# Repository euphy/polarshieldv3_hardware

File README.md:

View this project on [CADLAB.io](https://cadlab.io/project/1157). 

# polarshieldv3_hardware
Schematics, board and gerbers for Polarshield v3

Polarshield v3 is an aggregation board for connecting

* NodeMCU-32S
* 2x stepper drivers
* 320x240 LCD
* Touch panel
* SD card

v3.0e is the currently manufactured version that's inside recent PolargraphSD machines.

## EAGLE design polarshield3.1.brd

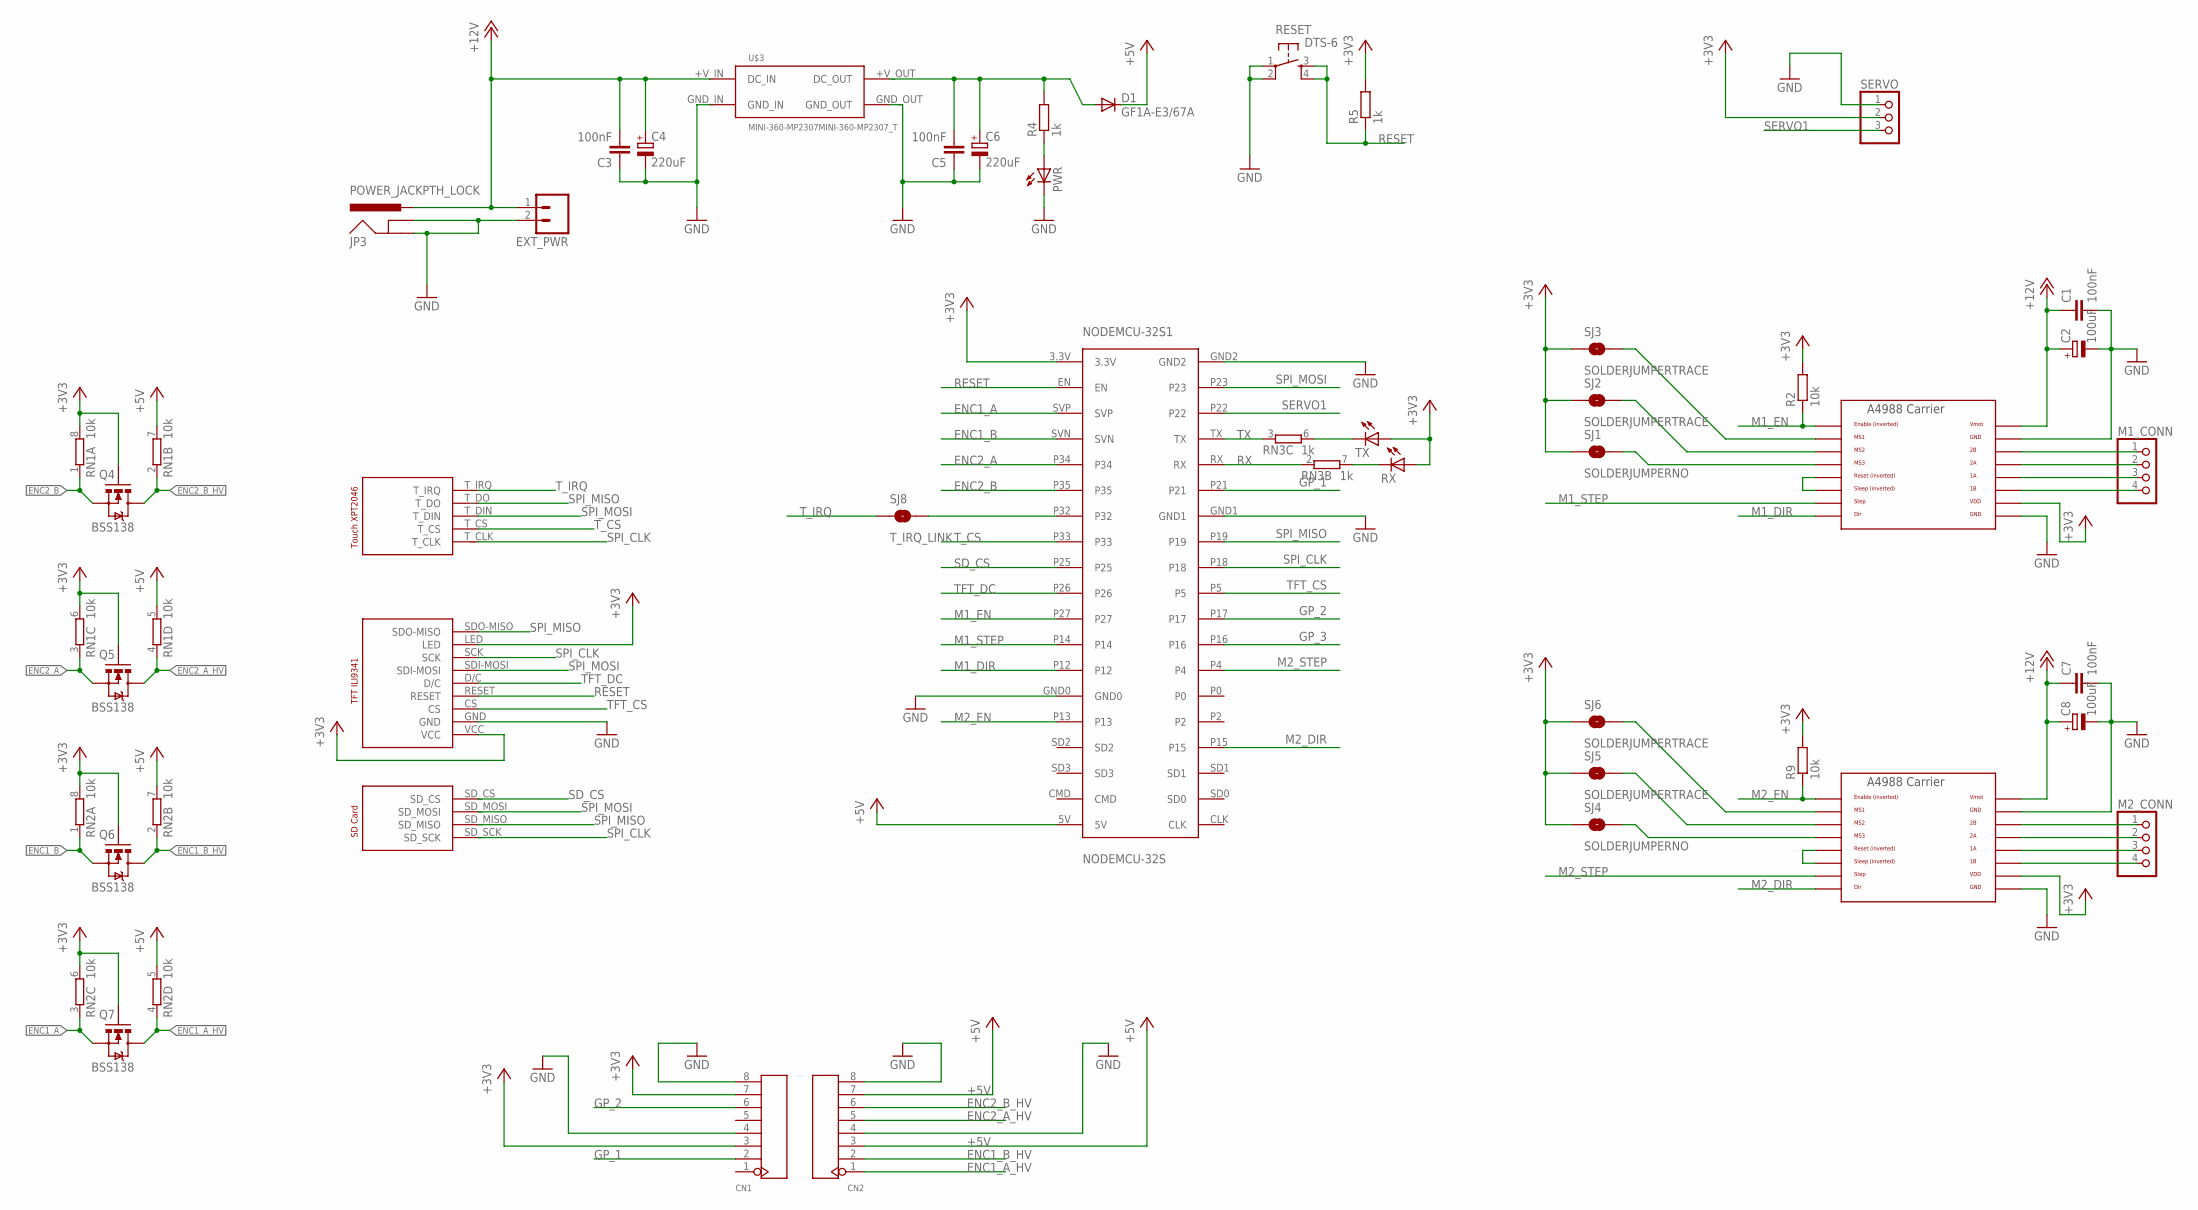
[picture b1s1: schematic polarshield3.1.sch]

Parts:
C1, C3, C5, C7: 100nF; C0805
C2, C8: 100uF; 153CLV-0605
C4, C6: 220uF; 153CLV-0605
CN1, CN2: DIP-BLACK-FEMALE-HEADER-VERT(8P-2.54); H8-2.54
D1: GF1A-E3/67A; DO214BA
EXT_PWR: M02PTH; 1X02
JP3: POWER_JACKPTH_LOCK; POWER_JACK_PTH_LOCK
M1_CONN, M2_CONN: PINHD-1X4/90; 1X04/90
MOTOR_1, MOTOR_2: A4988BREAKOUT
NODEMCU-32S1: NODEMCU-32S
PWR: LEDCHIPLED_0805; CHIPLED_0805
Q4, Q5, Q6, Q7: BSS138; SOT23-3
R2, R9: 10k; M0805
R4, R5: 1k; M0805
RESET: DTS-6
RN1, RN2: 10k; EXB38V
RN3: 1k; EXB38V
RX: LEDCHIPLED_0805; CHIPLED_0805
SERVO: PINHD-1X3/90; 1X03/90
SJ1, SJ4: SOLDERJUMPERNO; SJ_2S-NO
SJ2, SJ3, SJ5, SJ6: SOLDERJUMPERTRACE; SJ_2S-TRACE
SJ8: T_IRQ_LINK; SJ_2S-NO
TX: LEDCHIPLED_0805; CHIPLED_0805
U$2: 2.4_TFT_SPI_TOUCH_SD
U$3: MINI-360-MP2307MINI-360-MP2307_T; MINI-360-MP2307

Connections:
+3V3: CN1.3, CN1.7, MOTOR_1.VDD, MOTOR_2.VDD, NODEMCU-32S1.3.3V, Q4.1 (G), Q5.1 (G), Q6.1 (G), Q7.1 (G), R2.2, R5.2, R9.2, RN1.6 (2), RN1.8 (2), RN2.6 (2), RN2.8 (2), RX.A, SERVO.2, SJ1.1, SJ2.1, SJ3.1, SJ4.1, SJ5.1, SJ6.1, TX.A, U$2.LED, U$2.VCC
+5V: CN2.3, CN2.7, D1.C, NODEMCU-32S1.5V, RN1.5 (2), RN1.7 (2), RN2.5 (2), RN2.7 (2)
+12V: C1.1, C2.+, C3.2, C4.+, C7.1, C8.+, EXT_PWR.1, JP3.PWR, MOTOR_1.VMOT, MOTOR_2.VMOT, U$3.+V_IN (DC_IN)
ENC1_A: NODEMCU-32S1.SVP, Q7.2 (S), RN2.3 (1)
ENC1_A_HV: CN2.1, Q7.3 (D), RN2.4 (1)
ENC1_B: NODEMCU-32S1.SVN, Q6.2 (S), RN2.1
ENC1_B_HV: CN2.2, Q6.3 (D), RN2.2 (1)
ENC2_A: NODEMCU-32S1.P34, Q5.2 (S), RN1.3 (1)
ENC2_A_HV: CN2.5, Q5.3 (D), RN1.4 (1)
ENC2_B: NODEMCU-32S1.P35, Q4.2 (S), RN1.1
ENC2_B_HV: CN2.6, Q4.3 (D), RN1.2 (1)
GND: C1.2, C2.-, C3.1, C4.-, C5.1, C6.-, C7.2, C8.-, CN1.4, CN1.8, CN2.4, CN2.8, EXT_PWR.2, JP3.GND, JP3.GNDBREAK, MOTOR_1.GND, MOTOR_1.GND@0 (GND), MOTOR_2.GND, MOTOR_2.GND@0 (GND), NODEMCU-32S1.GND0, NODEMCU-32S1.GND1, NODEMCU-32S1.GND2, PWR.C, RESET.1, RESET.2, SERVO.1, U$2.GND, U$3.GND_IN, U$3.GND_OUT
GP_1: CN1.2, NODEMCU-32S1.P21
GP_2: CN1.6, NODEMCU-32S1.P17
GP_3: NODEMCU-32S1.P16
M1_DIR: MOTOR_1.DIR, NODEMCU-32S1.P12
M1_EN: MOTOR_1.EN, NODEMCU-32S1.P27, R2.1
M1_STEP: MOTOR_1.STEP, NODEMCU-32S1.P14
M2_DIR: MOTOR_2.DIR, NODEMCU-32S1.P15
M2_EN: MOTOR_2.EN, NODEMCU-32S1.P13, R9.1
M2_STEP: MOTOR_2.STEP, NODEMCU-32S1.P4
unnamed: NODEMCU-32S1.P32, SJ8.2
unnamed: MOTOR_1.RST, MOTOR_1.SLP (SLEEP)
unnamed: MOTOR_1.MS3, SJ1.2
unnamed: MOTOR_1.MS2, SJ2.2
unnamed: MOTOR_1.MS1, SJ3.2
unnamed: C5.2, C6.+, D1.A, R4.2, U$3.+V_OUT (DC_OUT)
unnamed: PWR.A, R4.1
unnamed: MOTOR_2.MS3, SJ4.2
unnamed: M1_CONN.1, MOTOR_1.2B
unnamed: M1_CONN.2, MOTOR_1.2A
unnamed: M1_CONN.3, MOTOR_1.1A
unnamed: M1_CONN.4, MOTOR_1.1B
unnamed: RN3.6 (2), TX.C
unnamed: RN3.7 (2), RX.C
unnamed: MOTOR_2.MS2, SJ5.2
unnamed: MOTOR_2.MS1, SJ6.2
unnamed: MOTOR_2.RST, MOTOR_2.SLP (SLEEP)
unnamed: M2_CONN.1, MOTOR_2.2B
unnamed: M2_CONN.2, MOTOR_2.2A
unnamed: M2_CONN.3, MOTOR_2.1A
unnamed: M2_CONN.4, MOTOR_2.1B
RESET: NODEMCU-32S1.EN, R5.1, RESET.3, RESET.4, U$2.RESET
RX: NODEMCU-32S1.RX, RN3.2 (1)
SD_CS: NODEMCU-32S1.P25, U$2.SD_CS
SERVO1: NODEMCU-32S1.P22, SERVO.3
SPI_CLK: NODEMCU-32S1.P18, U$2.SCK, U$2.SD_SCK, U$2.T_CLK
SPI_MISO: NODEMCU-32S1.P19, U$2.SDO-MISO, U$2.SD_MISO, U$2.T_DO
SPI_MOSI: NODEMCU-32S1.P23, U$2.SDI-MOSI, U$2.SD_MOSI, U$2.T_DIN
TFT_CS: NODEMCU-32S1.P5, U$2.CS
TFT_DC: NODEMCU-32S1.P26, U$2.D/C
TX: NODEMCU-32S1.TX, RN3.3 (1)
T_CS: NODEMCU-32S1.P33, U$2.T_CS
T_IRQ: SJ8.1, U$2.T_IRQ

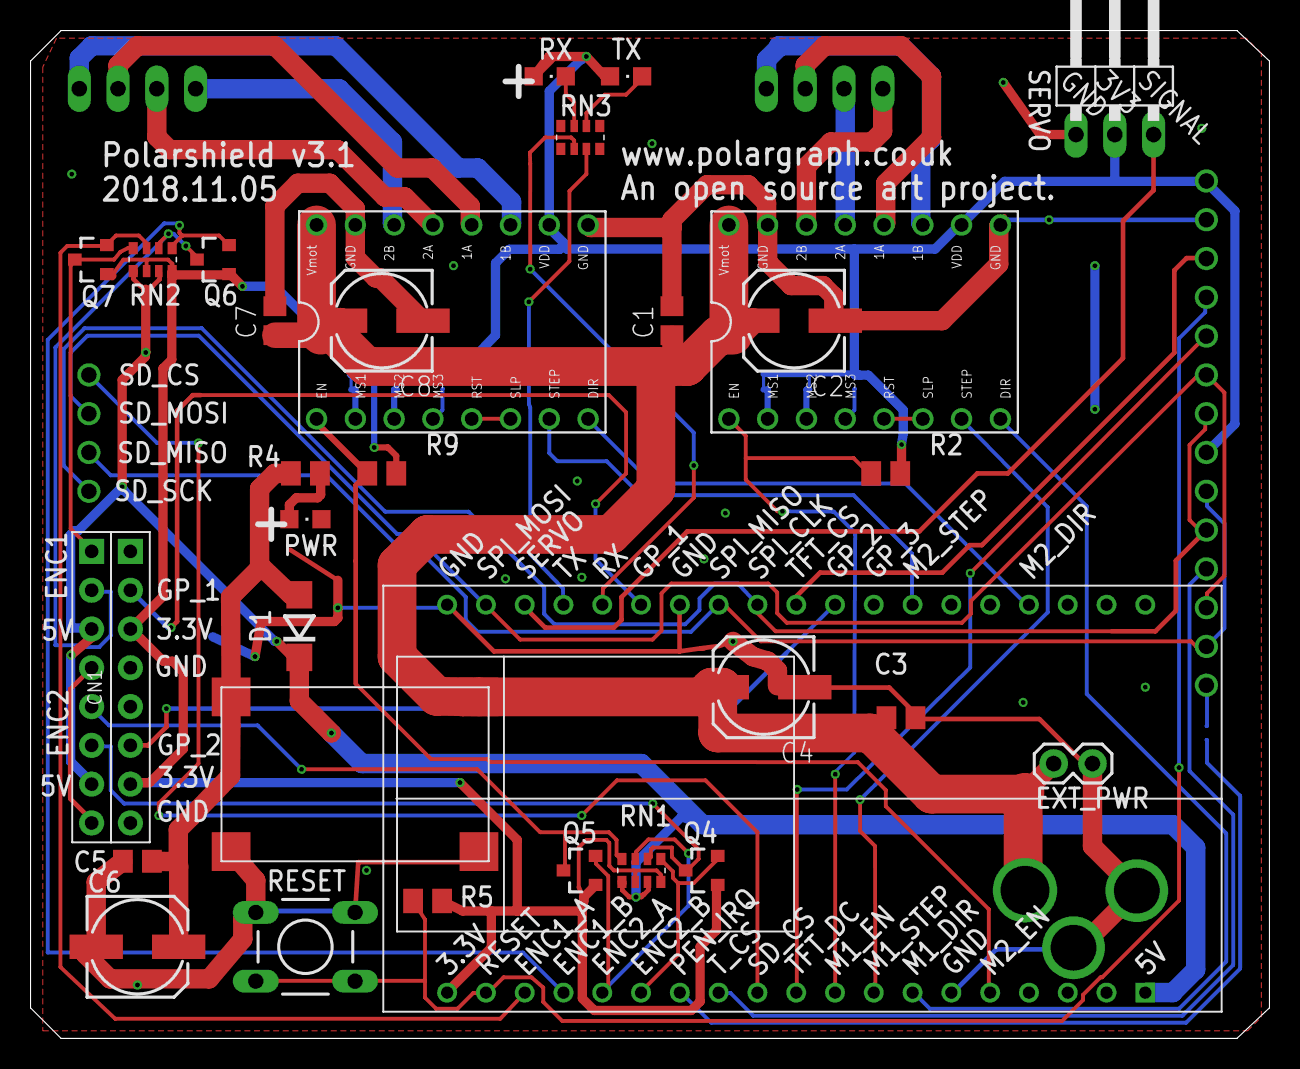
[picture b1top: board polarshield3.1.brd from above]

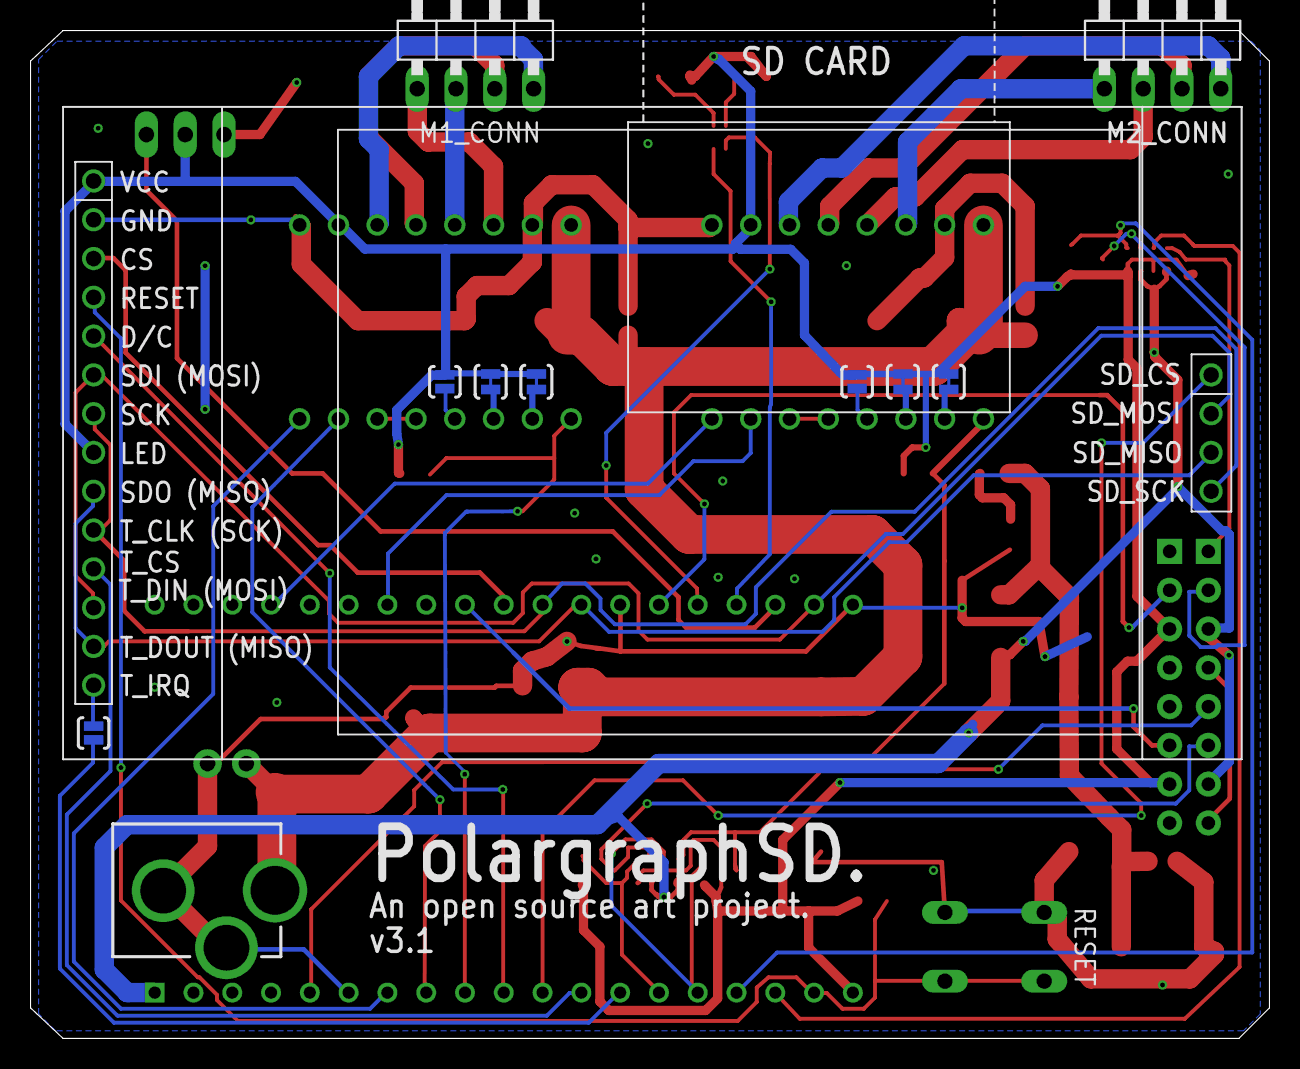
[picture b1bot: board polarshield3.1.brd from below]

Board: 2 copper layers, 81.1 x 66.0 mm, 43 parts (11 on the bottom side), 53 nets.

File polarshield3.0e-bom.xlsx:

Part | Value | Device | Package | Description | MF | MPN | OC_FARNELL | OC_NEWARK | PROD_ID | SF_ID | VALUE | OPTIONAL
C1 | 100nF | C-EUC0805 | C0805 | CAPACITOR, European symbol
C2 | 100uF | CPOL-EU153CLV-0605 | 153CLV-0605 | POLARIZED CAPACITOR, European symbol
C3 | 100nF | C-EUC0805 | C0805 | CAPACITOR, European symbol
C4 | 220uF | CPOL-EU153CLV-0605 | 153CLV-0605 | POLARIZED CAPACITOR, European symbol
C5 | 100nF | C-EUC0805 | C0805 | CAPACITOR, European symbol
C6 | 220uF | CPOL-EU153CLV-0605 | 153CLV-0605 | POLARIZED CAPACITOR, European symbol
C7 | 100nF | C-EUC0805 | C0805 | CAPACITOR, European symbol
C8 | 100uF | CPOL-EU153CLV-0605 | 153CLV-0605 | POLARIZED CAPACITOR, European symbol
D1 | GF1A-E3/67A | DIODE-DO214BA | DO214BA | DIODE |  | GF1A-E3/67A
EXT_PWR |  | M02PTH | 1X02 | Standard 2-pin 0.1" header. Use with |  |  |  |  |  |  |  | OPTIONAL
JP3 | POWER_JACKPTH_LOCK | POWER_JACKPTH_LOCK | POWER_JACK_PTH_LOCK | Power Jack |  |  |  |  | CONN-08197 | PRT-00119
PWR |  | LEDCHIPLED_0805 | CHIPLED_0805 | LED
TX |  | LEDCHIPLED_0805 | CHIPLED_0805 | LED
RX |  | LEDCHIPLED_0805 | CHIPLED_0805 | LED
Q4 | BSS138 | MOSFET-NCHANNELSMD | SOT23-3 |  |  |  |  |  |  |  |  | OPTIONAL
Q5 | BSS138 | MOSFET-NCHANNELSMD | SOT23-3 |  |  |  |  |  |  |  |  | OPTIONAL
Q6 | BSS138 | MOSFET-NCHANNELSMD | SOT23-3 |  |  |  |  |  |  |  |  | OPTIONAL
Q7 | BSS138 | MOSFET-NCHANNELSMD | SOT23-3 |  |  |  |  |  |  |  |  | OPTIONAL
R1 | 1k | R-EU_M0805 | M0805 | RESISTOR, European symbol
R2 | 10k | R-EU_M0805 | M0805 | RESISTOR, European symbol
R4 | 1k | R-EU_M0805 | M0805 | RESISTOR, European symbol
R5 | 1k | R-EU_M0805 | M0805 | RESISTOR, European symbol
R8 | 1k | R-EU_M0805 | M0805 | RESISTOR, European symbol
R9 | 10k | R-EU_M0805 | M0805 | RESISTOR, European symbol
RESET | DTS-6 | DTS-6 | DTS-6 |  |  | SKHHBYA010
RN1 | 10k | 4R-NEXB38V | EXB38V | Array Chip Resistor |  |  | unknown | unknown |  |  |  | OPTIONAL
RN2 | 10k | 4R-NEXB38V | EXB38V | Array Chip Resistor |  |  | unknown | unknown |  |  |  | OPTIONAL
RN3 | 1k | 4R-NEXB38V | EXB38V | Array Chip Resistor |  |  | unknown | unknown
SERVO |  | PINHD-1X3/90 | 1X03/90 | PIN HEADER
U$2 | 2.4_TFT_SPI_TOUCH_SD | 2.4_TFT_SPI_TOUCH_SD | 2.4_TFT_SPI_TOUCH_SD
U$3 | MINI-360-MP2307 | MINI-360-MP2307 | MINI-360-MP2307
M1_CONN |  | PINHD-1X4/90 | 1X04/90 | PIN HEADER |  | 1778641
M2_CONN |  | PINHD-1X4/90 | 1X04/90 | PIN HEADER |  | 1778641
CN1 |  | DIP-BLACK-FEMALE-HEADER-VERT(8P-2.54) | H8-2.54 | 320030061 |  | F185-1108A1BSYC1 |  |  |  |  | 8p-2.54 | OPTIONAL
CN2 |  | DIP-BLACK-FEMALE-HEADER-VERT(8P-2.54) | H8-2.54 | 320030061 |  | F185-1108A1BSYC1 |  |  |  |  | 8p-2.54 | OPTIONAL
MOTOR_1 | A4988BREAKOUT | A4988BREAKOUT | A4988BREAKOUT
MOTOR_2 | A4988BREAKOUT | A4988BREAKOUT | A4988BREAKOUT
NODEMCU-32S1 | NODEMCU-32S | NODEMCU-32S | NODEMCU-32S

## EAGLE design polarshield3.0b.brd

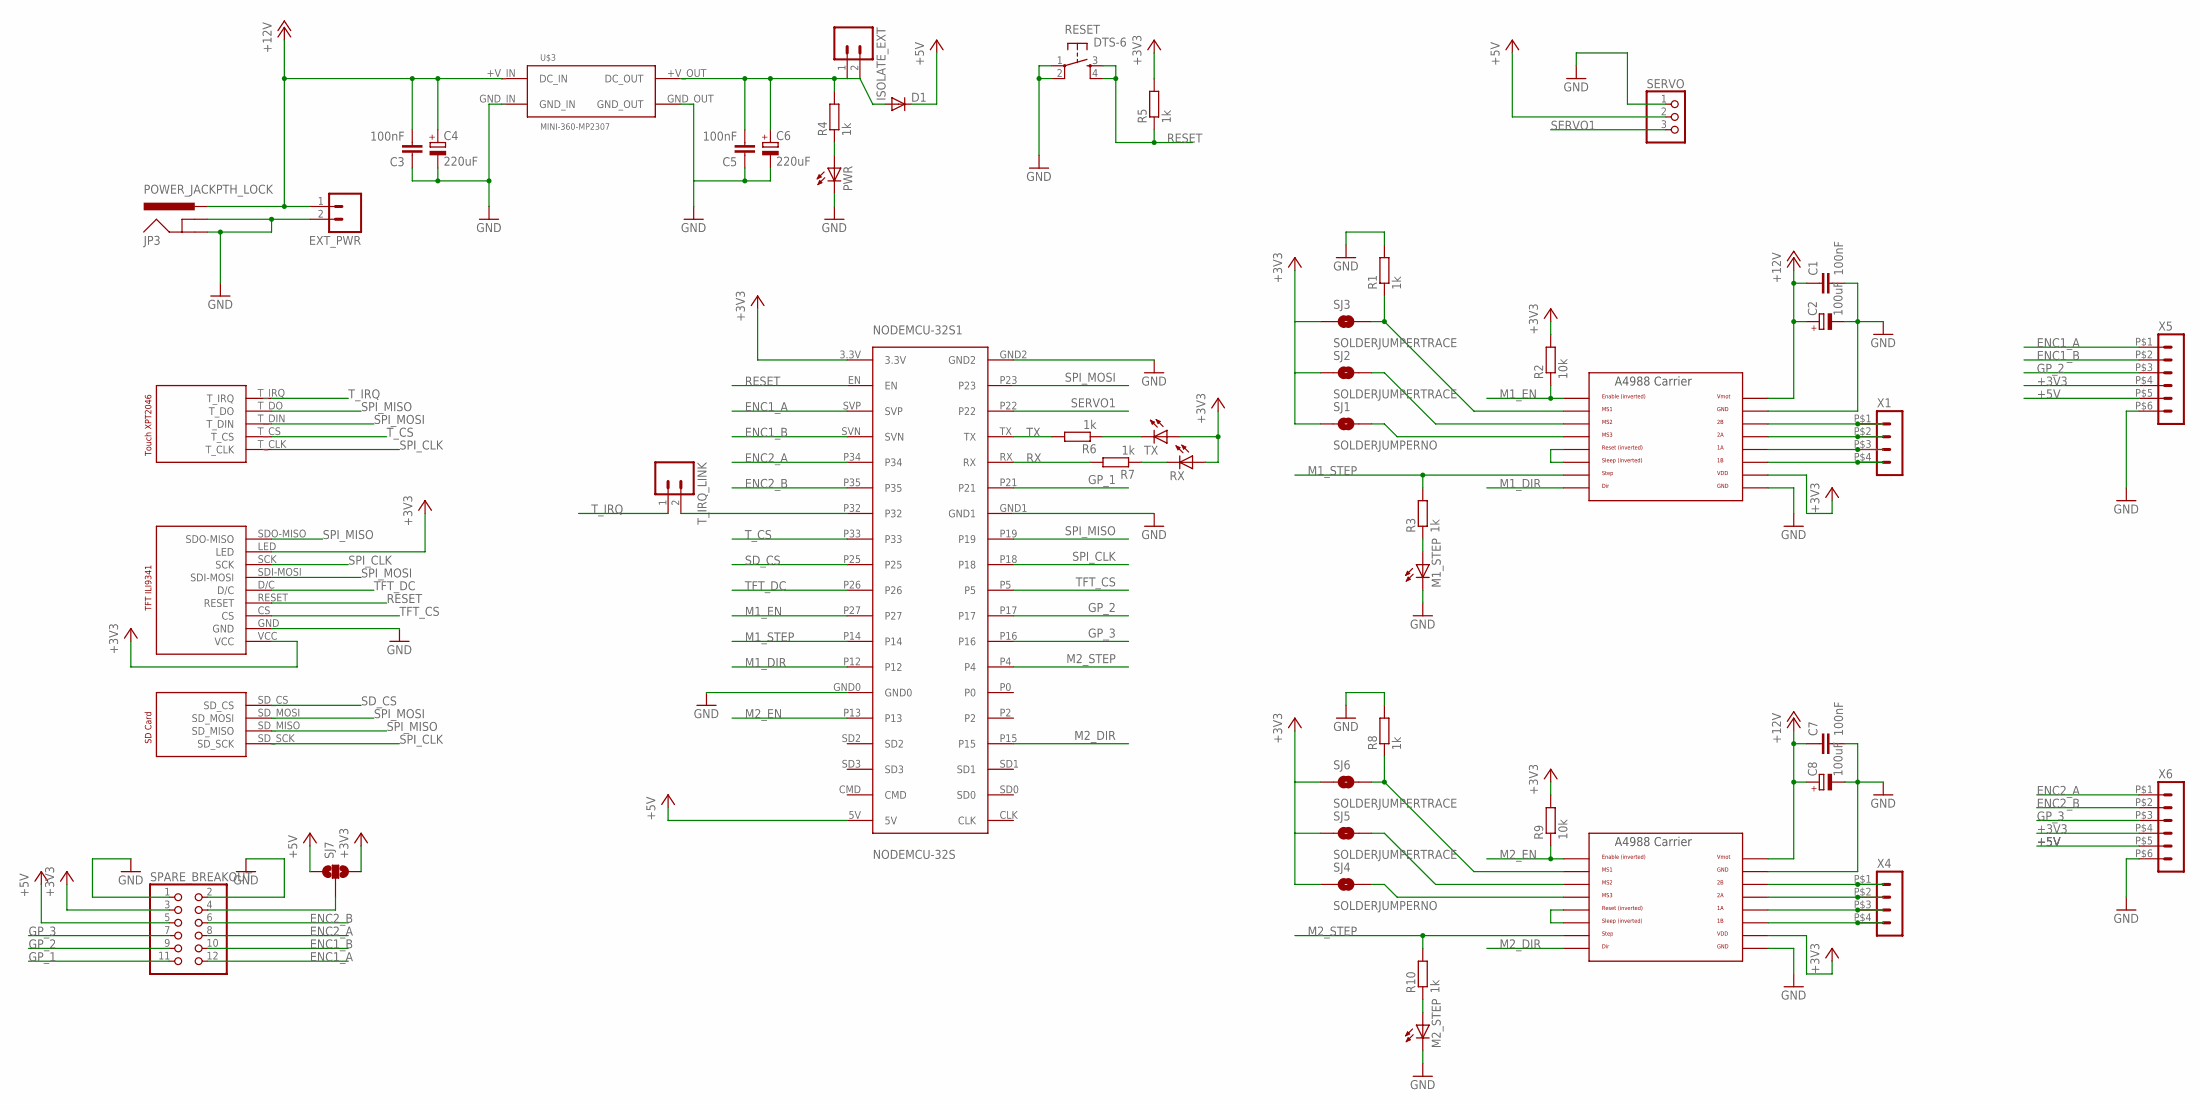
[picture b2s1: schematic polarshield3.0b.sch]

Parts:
C1, C3, C5, C7: 100nF; C0805
C2, C8: 100uF; 153CLV-0605
C4, C6: 220uF; 153CLV-0605
D1: DIODE-DO214BA; DO214BA
EXT_PWR: M02PTH; 1X02
ISOLATE_EXT: M02PTH; 1X02
JP3: POWER_JACKPTH_LOCK; POWER_JACK_PTH_LOCK
M1_STEP, M2_STEP: LEDCHIPLED_0805; CHIPLED_0805
MOTOR_1, MOTOR_2: A4988BREAKOUT
NODEMCU-32S1: NODEMCU-32S
PWR: LEDCHIPLED_0805; CHIPLED_0805
R1, R3, R4, R5, R6, R7, R8, R10: 1k; M0805
R2, R9: 10k; M0805
RESET: DTS-6
RX: LEDCHIPLED_0805; CHIPLED_0805
SERVO: PINHD-1X3/90; 1X03/90
SJ1, SJ4: SOLDERJUMPERNO; SJ_2S-NO
SJ2, SJ3, SJ5, SJ6: SOLDERJUMPERTRACE; SJ_2S-TRACE
SJ7: SOLDERJUMPER_2WAYPASTE1&2; SJ_3_PASTE1&2
SPARE_BREAKOUT: PINHD-2X6; 2X06
TX: LEDCHIPLED_0805; CHIPLED_0805
T_IRQ_LINK: M02PTH; 1X02
U$2: 2.4_TFT_SPI_TOUCH_SD
U$3: MINI-360-MP2307
X1, X4: HEADER_POS4_43045-0401; 43045-0400
X5, X6: HEADER_POS6_43045-0600; 43045-0600

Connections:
+3V3: MOTOR_1.VDD, MOTOR_2.VDD, NODEMCU-32S1.3.3V, R2.2, R5.2, R9.2, RX.A, SJ1.1, SJ2.1, SJ3.1, SJ4.1, SJ5.1, SJ6.1, SJ7.3, SPARE_BREAKOUT.3, TX.A, U$2.LED, U$2.VCC, X5.P$4 (4), X6.P$4 (4)
+5V: D1.C, NODEMCU-32S1.5V, SERVO.2, SJ7.1, SPARE_BREAKOUT.5, X5.P$5 (5), X6.P$5 (5)
+12V: C1.1, C2.+, C3.2, C4.+, C7.1, C8.+, EXT_PWR.1, JP3.PWR, MOTOR_1.VMOT, MOTOR_2.VMOT, U$3.+V_IN (DC_IN)
ENC1_A: NODEMCU-32S1.SVP, SPARE_BREAKOUT.12, X5.P$1 (1)
ENC1_B: NODEMCU-32S1.SVN, SPARE_BREAKOUT.10, X5.P$2 (2)
ENC2_A: NODEMCU-32S1.P34, SPARE_BREAKOUT.8, X6.P$1 (1)
ENC2_B: NODEMCU-32S1.P35, SPARE_BREAKOUT.6, X6.P$2 (2)
GND: C1.2, C2.-, C3.1, C4.-, C5.1, C6.-, C7.2, C8.-, EXT_PWR.2, JP3.GND, JP3.GNDBREAK, M1_STEP.C, M2_STEP.C, MOTOR_1.GND, MOTOR_1.GND@0 (GND), MOTOR_2.GND, MOTOR_2.GND@0 (GND), NODEMCU-32S1.GND0, NODEMCU-32S1.GND1, NODEMCU-32S1.GND2, PWR.C, R1.2, R8.2, RESET.1, RESET.2, SERVO.1, SPARE_BREAKOUT.1, SPARE_BREAKOUT.2, U$2.GND, U$3.GND_IN, U$3.GND_OUT, X5.P$6 (6), X6.P$6 (6)
GP_1: NODEMCU-32S1.P21, SPARE_BREAKOUT.11
GP_2: NODEMCU-32S1.P17, SPARE_BREAKOUT.9, X5.P$3 (3)
GP_3: NODEMCU-32S1.P16, SPARE_BREAKOUT.7, X6.P$3 (3)
M1_DIR: MOTOR_1.DIR, NODEMCU-32S1.P12
M1_EN: MOTOR_1.EN, NODEMCU-32S1.P27, R2.1
M1_STEP: MOTOR_1.STEP, NODEMCU-32S1.P14, R3.2
M2_DIR: MOTOR_2.DIR, NODEMCU-32S1.P15
M2_EN: MOTOR_2.EN, NODEMCU-32S1.P13, R9.1
M2_STEP: MOTOR_2.STEP, NODEMCU-32S1.P4, R10.2
unnamed: NODEMCU-32S1.P32, T_IRQ_LINK.2
unnamed: MOTOR_1.RST, MOTOR_1.SLP (SLEEP)
unnamed: MOTOR_1.MS3, SJ1.2
unnamed: MOTOR_1.MS2, SJ2.2
unnamed: MOTOR_1.MS1, R1.1, SJ3.2
unnamed: M1_STEP.A, R3.1
unnamed: C5.2, C6.+, D1.A, ISOLATE_EXT.1, ISOLATE_EXT.2, R4.2, U$3.+V_OUT (DC_OUT)
unnamed: PWR.A, R4.1
unnamed: MOTOR_2.MS3, SJ4.2
unnamed: MOTOR_1.2B, X1.P$1 (1)
unnamed: MOTOR_1.2A, X1.P$2 (2)
unnamed: MOTOR_1.1A, X1.P$3 (3)
unnamed: MOTOR_1.1B, X1.P$4 (4)
unnamed: R6.1, TX.C
unnamed: R7.1, RX.C
unnamed: MOTOR_2.MS2, SJ5.2
unnamed: MOTOR_2.MS1, R8.1, SJ6.2
unnamed: MOTOR_2.RST, MOTOR_2.SLP (SLEEP)
unnamed: M2_STEP.A, R10.1
unnamed: MOTOR_2.1B, X4.P$4 (4)
unnamed: MOTOR_2.2B, X4.P$1 (1)
unnamed: MOTOR_2.2A, X4.P$2 (2)
unnamed: MOTOR_2.1A, X4.P$3 (3)
unnamed: SJ7.2, SPARE_BREAKOUT.4
RESET: NODEMCU-32S1.EN, R5.1, RESET.3, RESET.4, U$2.RESET
RX: NODEMCU-32S1.RX, R7.2
SD_CS: NODEMCU-32S1.P25, U$2.SD_CS
SERVO1: NODEMCU-32S1.P22, SERVO.3
SPI_CLK: NODEMCU-32S1.P18, U$2.SCK, U$2.SD_SCK, U$2.T_CLK
SPI_MISO: NODEMCU-32S1.P19, U$2.SDO-MISO, U$2.SD_MISO, U$2.T_DO
SPI_MOSI: NODEMCU-32S1.P23, U$2.SDI-MOSI, U$2.SD_MOSI, U$2.T_DIN
TFT_CS: NODEMCU-32S1.P5, U$2.CS
TFT_DC: NODEMCU-32S1.P26, U$2.D/C
TX: NODEMCU-32S1.TX, R6.2
T_CS: NODEMCU-32S1.P33, U$2.T_CS
T_IRQ: T_IRQ_LINK.1, U$2.T_IRQ

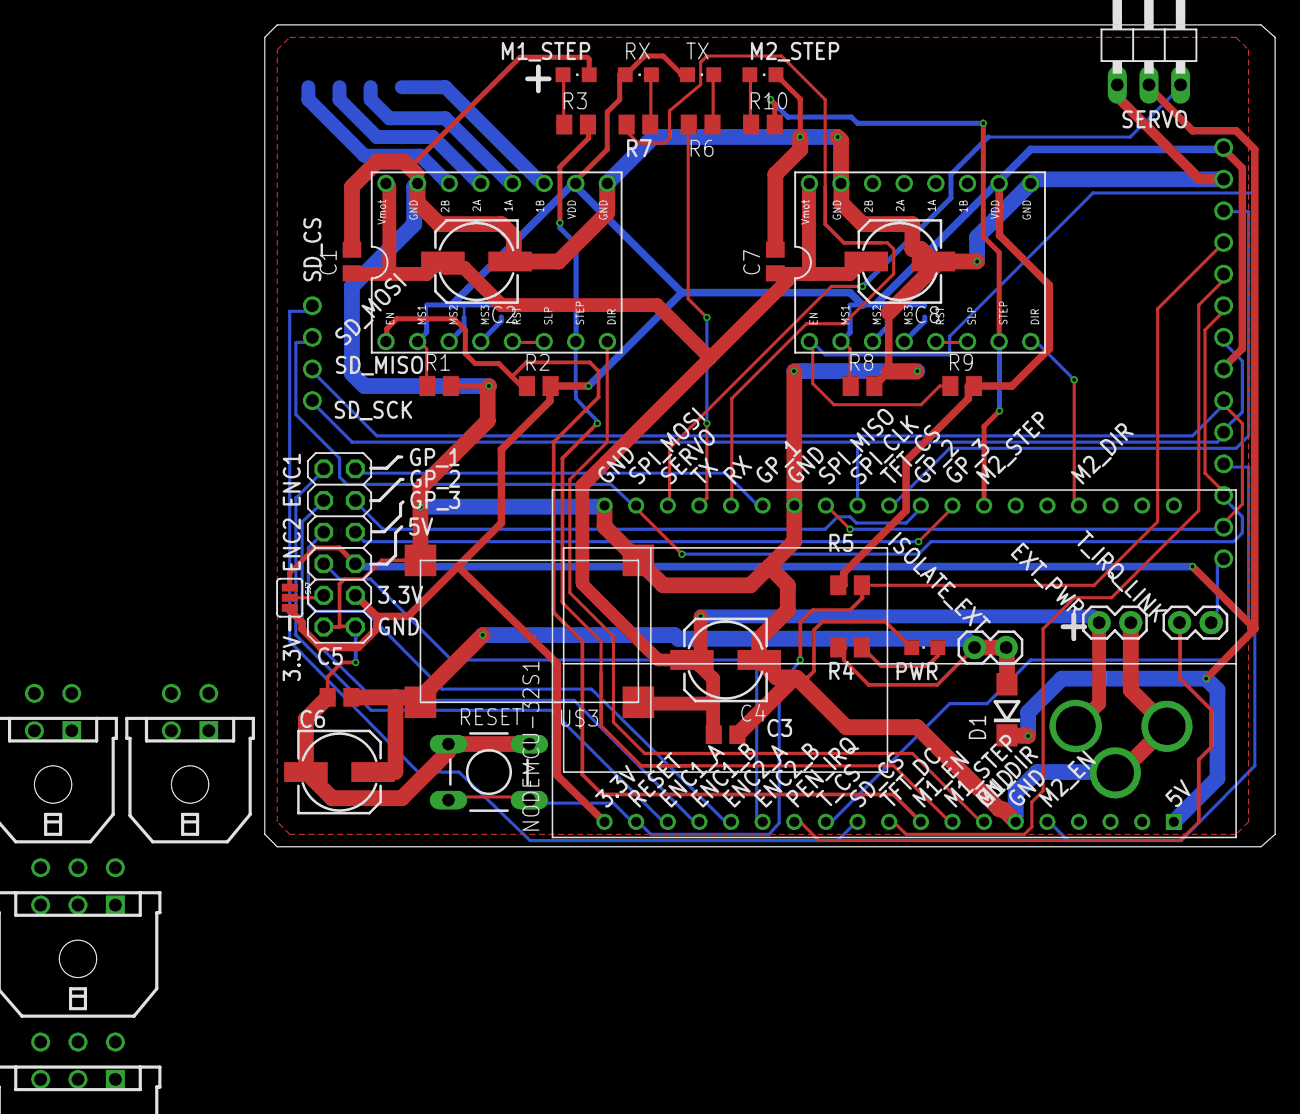
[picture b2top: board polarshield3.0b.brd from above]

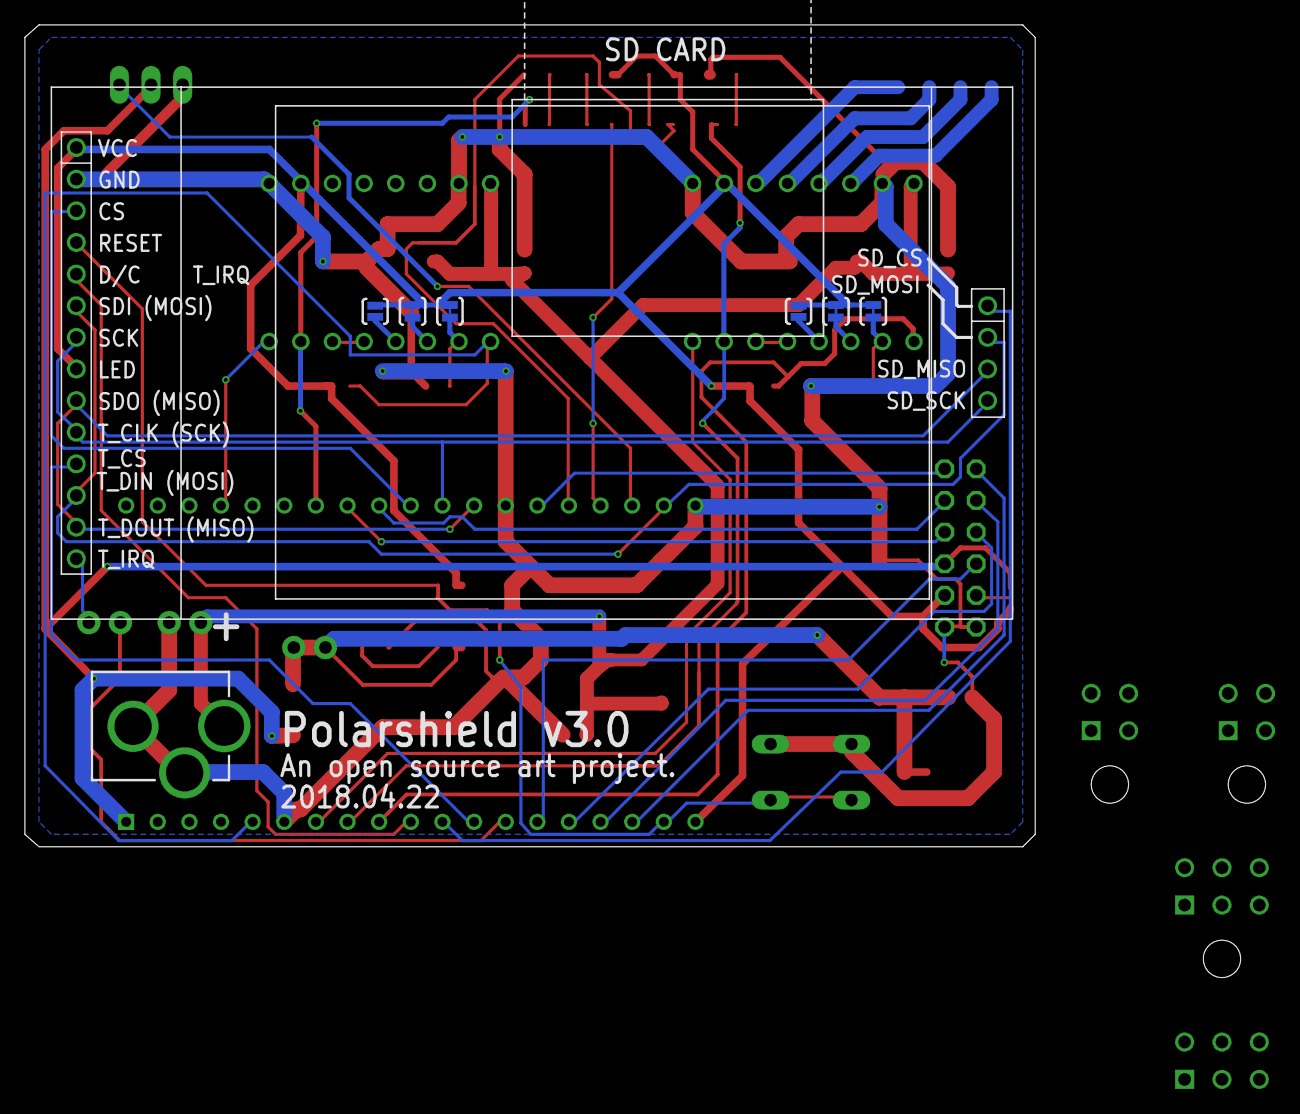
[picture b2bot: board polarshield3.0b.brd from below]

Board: 2 copper layers, 81.1 x 66.0 mm, 47 parts (8 on the bottom side), 53 nets.

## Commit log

2018-04-15 Initial files
2018-04-22 first version looks ok visually
2018-04-22 Built gerbers
2018-04-22 eagle update
2018-06-10 Minor changes based on first board.
2018-06-10 Backlink to CADLAB.io has been added.
2018-06-10 Gerbers for v3.0e
2018-06-11 v3.0e rebuilt
2018-10-02 3.0f removed 100k resistor from MS1 pin.
2018-10-26 Added part number GF1A-E3/67A to D1, #1
2018-10-26 Added bom, closes #1
2018-11-03 v3.0f. Removed 1k resistors, moved motor connectors and pads for mini-360.
2018-11-03 v3.1 changed servo supply voltage to 3.3v
2018-11-16 v3.1 - replaced 5v servo power supply with 3.3v
2018-11-16 adding mouser bom

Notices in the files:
parts and their libraries:
SparkFun-Connectors: Licensing: Creative Commons ShareAlike 4.0 International - https://creativecommons.org/licenses/by-sa/4.0
